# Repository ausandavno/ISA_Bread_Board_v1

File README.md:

# ISA_Bread_Board_v1
A plug-in board designed to house breadboard components to allow easy prototyping on an 8-bit ISA data bus. 

Current version v1.1

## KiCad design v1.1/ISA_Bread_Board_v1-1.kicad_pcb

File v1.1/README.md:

# ISA_Bread_Board_v1.1
Version 1.1 of a plug-in board designed to house breadboard components to allow easy prototyping on an 8-bit ISA data bus.

Board render:

Constructed board (older version; ignore version number, ignore loaded components in breadboard):

## Hardware Documentation

### Schematic and PCB Layout

[Schematics - Version 1.1 (pdf)](../v1.1/Schematics/ISA_Bread_Board_v1.1-Schematics.pdf)

[PCB Layout - Version 1.1 (zip)](../v1.1/PCB_Layout/ISA_Bread_Board_v1.1-PCB_Layout.zip)

[Gerbers - Version 1.1 (zip)](../v1.1/Gerbers/ISA_Bread_Board_v1-1-Gerbers.zip)

### Breadboard Components

Designed to house breadboard modules of "standard" size:
* Main Module:
  * 10 Columns, 63 Rows
  * 35.56mm wide (excluding interconnect lugs), 165.1mm long
* Power Rail Module:
  * 9.525mm wide (excluding interconnect lugs), 165.1mm long  

Designed to house two main modules and three power rails on each side of the pcb, if desired.

Absolute maximum board area in which to stick breadboard modules is 103.63mm wide by 167.26mm long.

### Bill of Materials - v1.1

Component type     | Reference | Description            | Quantity | Possible sources and notes 
------------------ | --------- | ---------------------- | -------- | --------------------------
PCB                |           | ISA Post Card v1.1     | 1        | Use supplied Gerber or KiCad files to order from your perferred PCB fabrication house
Breadboard |         | Choose to your preference. Up to two main modules and three power rails on each side of pcb. Suggested Mouser part has not been tested. Suggested to purchase two units per side of pcb desired, and discard one of the power rails.|          | Mouser [BB830](https://au.mouser.com/ProductDetail/854-BB830)
Capacitor   | C1 - C6  | P5.08mm 4.7uF 25V  | 6        | Mouser [FG28X5R1E475KRT00](https://au.mouser.com/ProductDetail/810-FG28X5R1E475KRT0)
Header | J3-J8    | Female Header 02x02   | 6        | Use 1x40 female turned pin strip (2.54mm Pitch) or specific header
Header | J9    | Female Header 02x31   | 1        | Use 1x40 female turned pin strip (2.54mm Pitch) or specific header
Header | J10    | Female Header 02x20   | 1        | Use 1x40 female turned pin strip (2.54mm Pitch) or specific header
Header | J11    | Female Header 02x08   | 1        | Use 1x40 female turned pin strip (2.54mm Pitch) or specific header
Header | J12    | Female Header 02x07   | 1        | Use 1x40 female turned pin strip (2.54mm Pitch) or specific header

## Changes
* Version 1.1
  * First Issue

## Known Issues
* Version 1.1
  * None at present
 
## Open Hardware License
 
You may redistribute and modify this Covered Source, and make products using it, under the terms of the CERN-OHL-P v2 (https:/cern.ch/cern-ohl). This Covered Source is distributed WITHOUT ANY EXPRESS OR IMPLIED WARRANTY, INCLUDING OF MERCHANTABILITY, SATISFACTORY QUALITY AND FITNESS FOR A PARTICULAR PURPOSE. Please see the CERN-OHL-P v2 for applicable conditions.
 
Warranty Disclaimed per 5.1 of CERN-OHL-P v2.
 
Liability Excluded and Limited per 5.2 of CERN-OHL-P v2.
 
See "LICENSE_NOTICES_and_CHANGES.txt" for specific Notices relating to this hardware design.

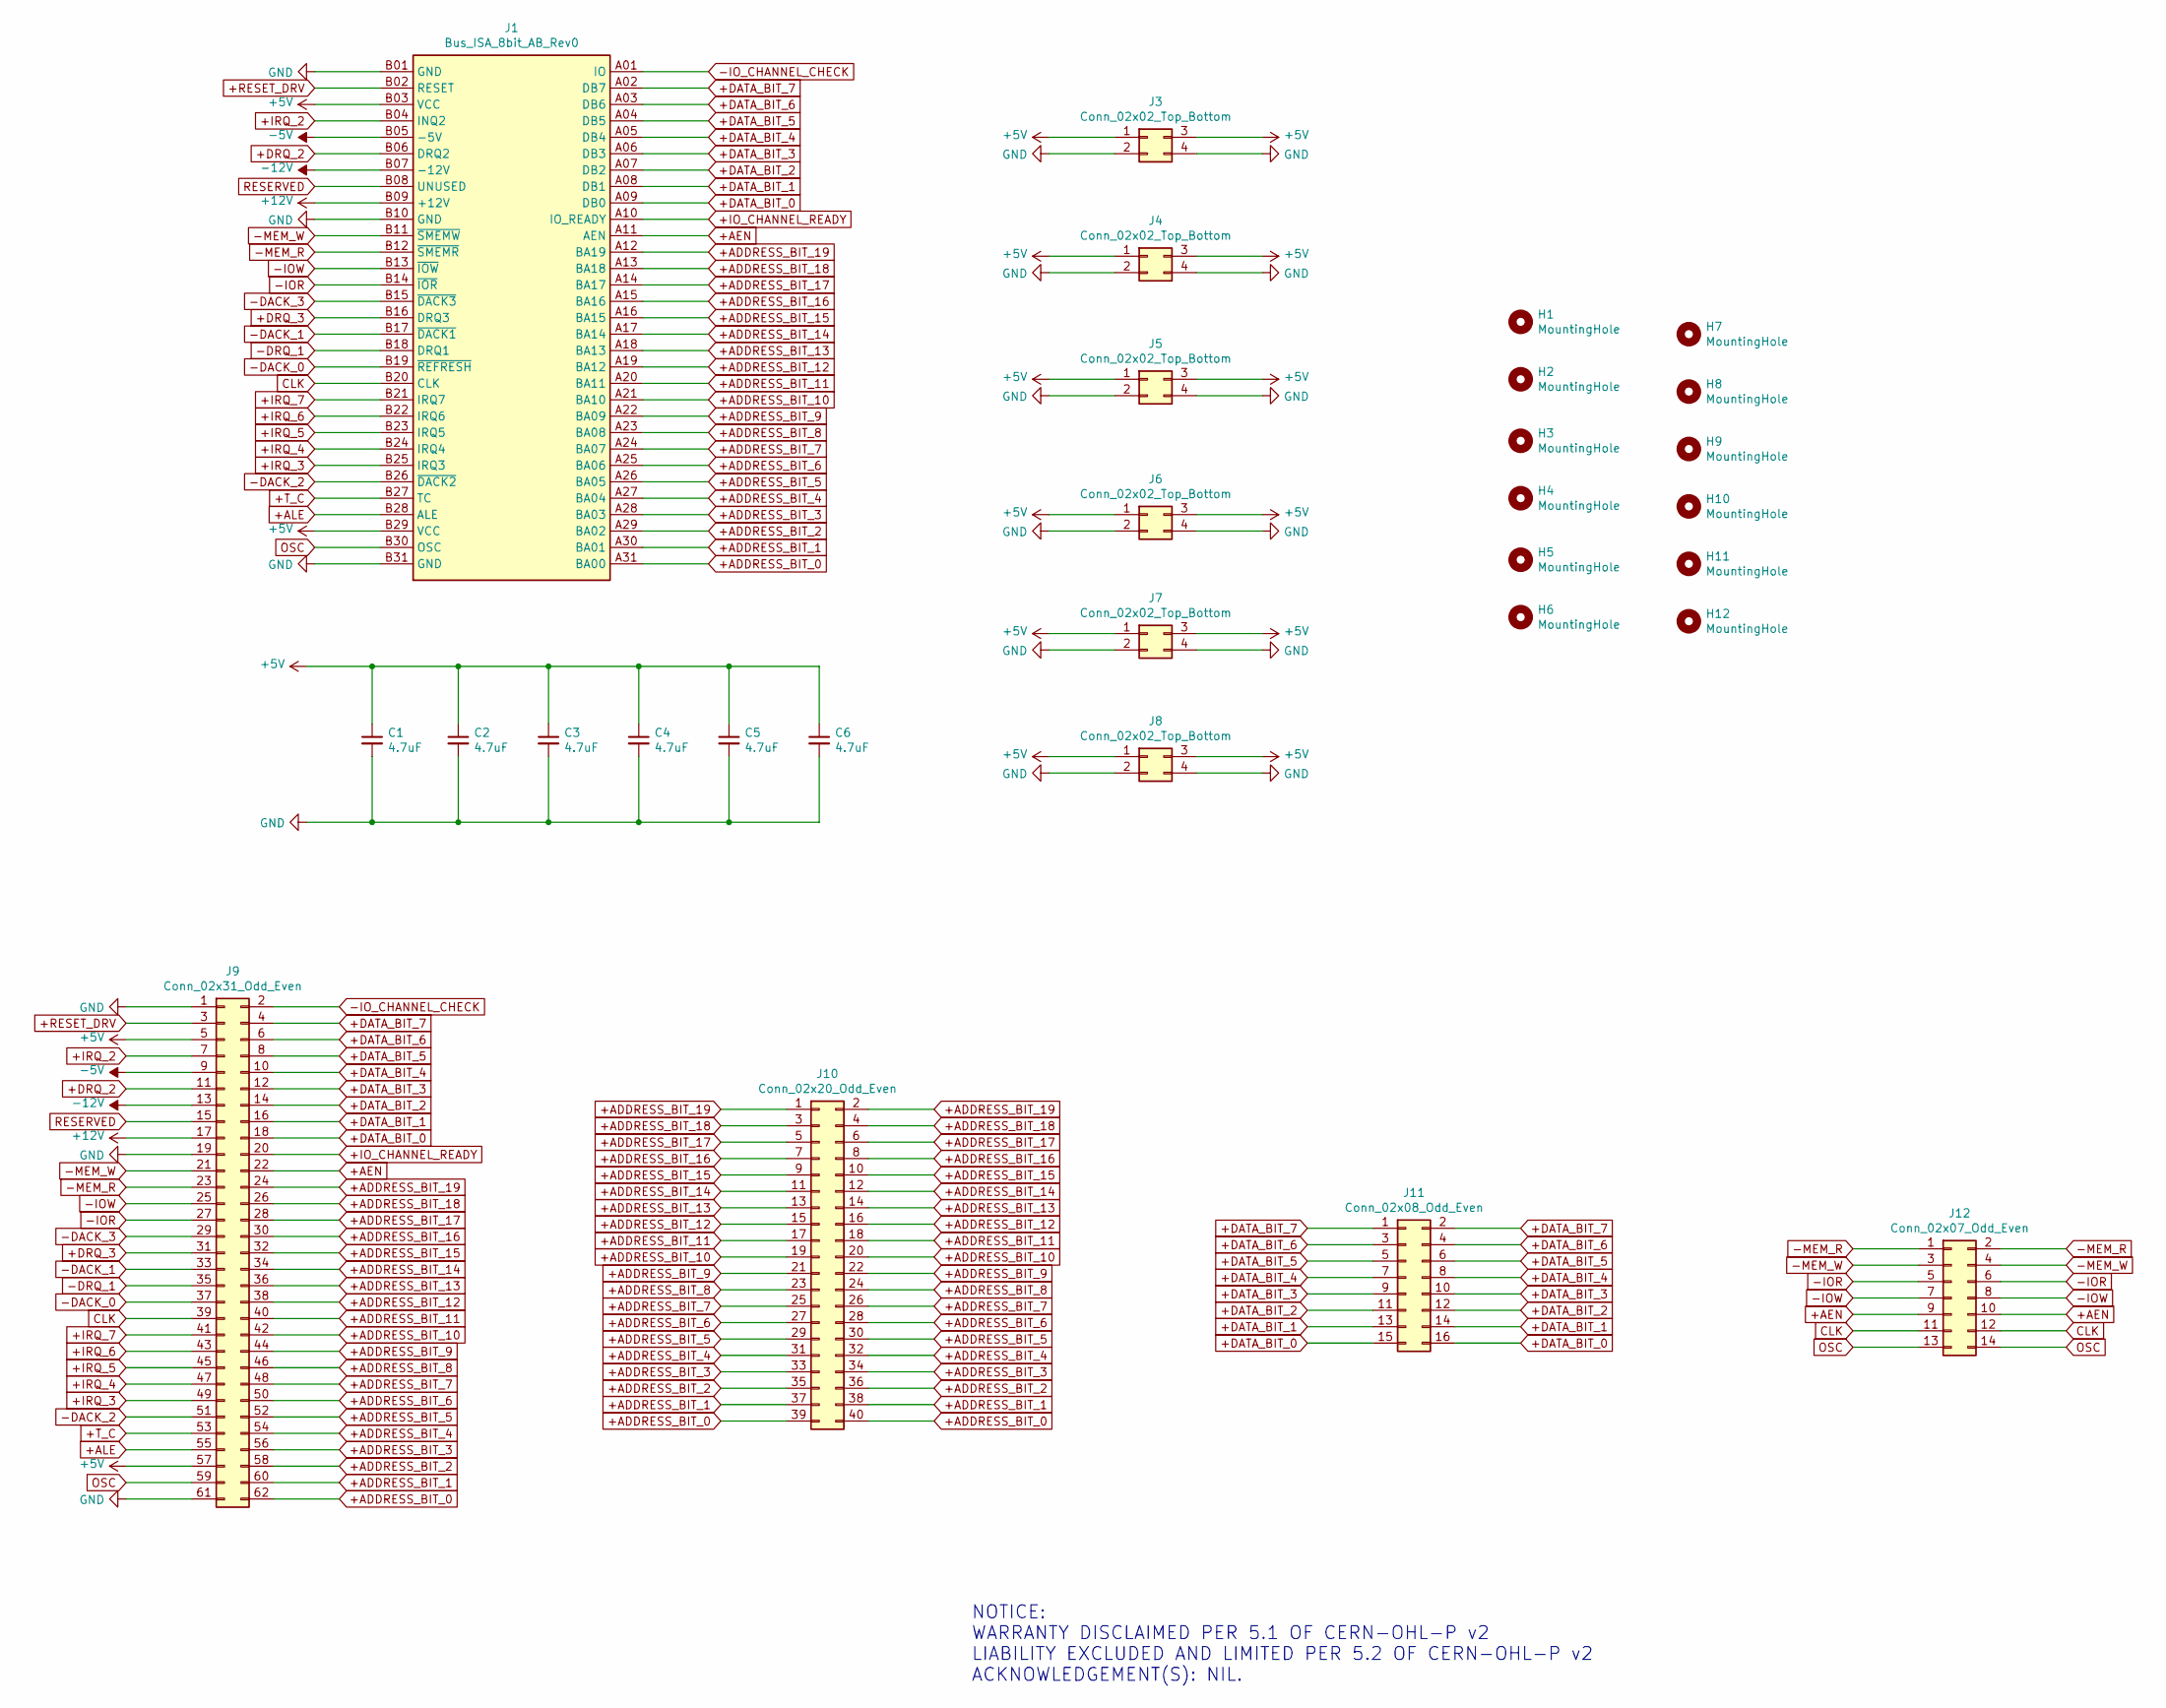
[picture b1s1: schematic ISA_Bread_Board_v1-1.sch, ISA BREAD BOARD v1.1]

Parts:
C1, C2, C3, C4, C5, C6: 4.7uF; C_Disc_D5.0mm_W2.5mm_P5.00mm
H1, H2, H3, H4, H5, H6, H7, H8, H9, H10, H11, H12: MountingHole; MountingHole_4mm
J1: Bus_ISA_8bit_AB_Rev0; ISA_CARD_EDGE_CONNECTOR_8BIT_Rev1
J3, J4, J5, J6, J7, J8: Conn_02x02_Top_Bottom; PinSocket_2x02_P2.54mm_Vertical
J9: Conn_02x31_Odd_Even; PinSocket_2x31_P2.54mm_Vertical
J10: Conn_02x20_Odd_Even; PinSocket_2x20_P2.54mm_Vertical
J11: Conn_02x08_Odd_Even; PinSocket_2x08_P2.54mm_Vertical
J12: Conn_02x07_Odd_Even; PinSocket_2x07_P2.54mm_Vertical

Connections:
+5V: C1.1, C2.1, C3.1, C4.1, C5.1, C6.1, J1.B03 (VCC), J1.B29 (VCC), J3.1, J3.3, J4.1, J4.3, J5.1, J5.3, J6.1, J6.3, J7.1, J7.3, J8.1, J8.3, J9.5, J9.57
+12V: J1.B09 (+12V), J9.17
+ADDRESS_BIT_0: J1.A31 (BA00), J9.62, J10.39, J10.40
+ADDRESS_BIT_1: J1.A30 (BA01), J9.60, J10.37, J10.38
+ADDRESS_BIT_2: J1.A29 (BA02), J9.58, J10.35, J10.36
+ADDRESS_BIT_3: J1.A28 (BA03), J9.56, J10.33, J10.34
+ADDRESS_BIT_4: J1.A27 (BA04), J9.54, J10.31, J10.32
+ADDRESS_BIT_5: J1.A26 (BA05), J9.52, J10.29, J10.30
+ADDRESS_BIT_6: J1.A25 (BA06), J9.50, J10.27, J10.28
+ADDRESS_BIT_7: J1.A24 (BA07), J9.48, J10.25, J10.26
+ADDRESS_BIT_8: J1.A23 (BA08), J9.46, J10.23, J10.24
+ADDRESS_BIT_9: J1.A22 (BA09), J9.44, J10.21, J10.22
+ADDRESS_BIT_10: J1.A21 (BA10), J9.42, J10.19, J10.20
+ADDRESS_BIT_11: J1.A20 (BA11), J9.40, J10.17, J10.18
+ADDRESS_BIT_12: J1.A19 (BA12), J9.38, J10.15, J10.16
+ADDRESS_BIT_13: J1.A18 (BA13), J9.36, J10.13, J10.14
+ADDRESS_BIT_14: J1.A17 (BA14), J9.34, J10.11, J10.12
+ADDRESS_BIT_15: J1.A16 (BA15), J9.32, J10.9, J10.10
+ADDRESS_BIT_16: J1.A15 (BA16), J9.30, J10.7, J10.8
+ADDRESS_BIT_17: J1.A14 (BA17), J9.28, J10.5, J10.6
+ADDRESS_BIT_18: J1.A13 (BA18), J9.26, J10.3, J10.4
+ADDRESS_BIT_19: J1.A12 (BA19), J9.24, J10.1, J10.2
+AEN: J1.A11 (AEN), J9.22, J12.9, J12.10
+ALE: J1.B28 (ALE), J9.55
+DATA_BIT_0: J1.A09 (DB0), J9.18, J11.15, J11.16
+DATA_BIT_1: J1.A08 (DB1), J9.16, J11.13, J11.14
+DATA_BIT_2: J1.A07 (DB2), J9.14, J11.11, J11.12
+DATA_BIT_3: J1.A06 (DB3), J9.12, J11.9, J11.10
+DATA_BIT_4: J1.A05 (DB4), J9.10, J11.7, J11.8
+DATA_BIT_5: J1.A04 (DB5), J9.8, J11.5, J11.6
+DATA_BIT_6: J1.A03 (DB6), J9.6, J11.3, J11.4
+DATA_BIT_7: J1.A02 (DB7), J9.4, J11.1, J11.2
+DRQ_2: J1.B06 (DRQ2), J9.11
+DRQ_3: J1.B16 (DRQ3), J9.31
+IO_CHANNEL_READY: J1.A10 (IO_READY), J9.20
+IRQ_2: J1.B04 (INQ2), J9.7
+IRQ_3: J1.B25 (IRQ3), J9.49
+IRQ_4: J1.B24 (IRQ4), J9.47
+IRQ_5: J1.B23 (IRQ5), J9.45
+IRQ_6: J1.B22 (IRQ6), J9.43
+IRQ_7: J1.B21 (IRQ7), J9.41
+RESET_DRV: J1.B02 (RESET), J9.3
+T_C: J1.B27 (TC), J9.53
-5V: J1.B05 (-5V), J9.9
-12V: J1.B07 (-12V), J9.13
-DACK_0: J1.B19 (~REFRESH), J9.37
-DACK_1: J1.B17 (~DACK1), J9.33
-DACK_2: J1.B26 (~DACK2), J9.51
-DACK_3: J1.B15 (~DACK3), J9.29
-DRQ_1: J1.B18 (DRQ1), J9.35
-IOR: J1.B14 (~IOR), J9.27, J12.5, J12.6
-IOW: J1.B13 (~IOW), J9.25, J12.7, J12.8
-IO_CHANNEL_CHECK: J1.A01 (IO), J9.2
-MEM_R: J1.B12 (~SMEMR), J9.23, J12.1, J12.2
-MEM_W: J1.B11 (~SMEMW), J9.21, J12.3, J12.4
CLK: J1.B20 (CLK), J9.39, J12.11, J12.12
GND: C1.2, C2.2, C3.2, C4.2, C5.2, C6.2, J1.B01 (GND), J1.B10 (GND), J1.B31 (GND), J3.2, J3.4, J4.2, J4.4, J5.2, J5.4, J6.2, J6.4, J7.2, J7.4, J8.2, J8.4, J9.1, J9.19, J9.61
OSC: J1.B30 (OSC), J9.59, J12.13, J12.14
RESERVED: J1.B08 (UNUSED), J9.15

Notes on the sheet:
NOTICE: WARRANTY DISCLAIMED PER 5.1 OF CERN-OHL-P v2 LIABILITY EXCLUDED AND LIMITED PER 5.2 OF CERN-OHL-P v2 ACKNOWLEDGEMENT(S): NIL.

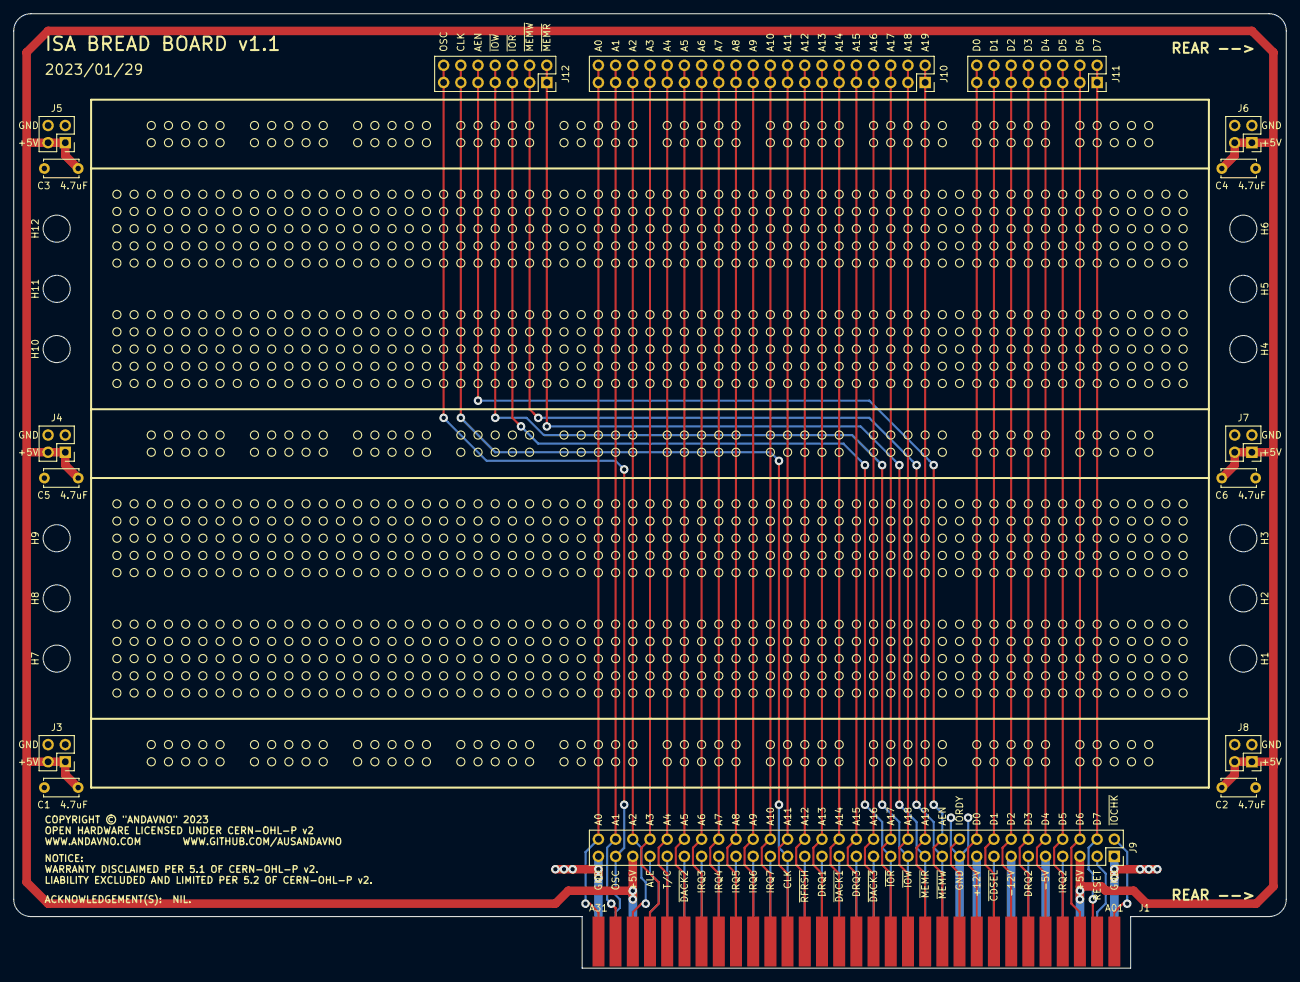
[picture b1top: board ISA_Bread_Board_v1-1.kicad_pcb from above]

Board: 2 copper layers, 188.0 x 141.0 mm, 29 parts (0 on the bottom side), 59 nets.

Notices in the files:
v1.1/ISA_Bread_Board_v1-1.kicad_pcb:
COPYRIGHT © \"ANDAVNO\" 2023
OPEN HARDWARE LICENSED UNDER CERN-OHL-P v2
